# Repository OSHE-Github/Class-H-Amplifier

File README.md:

# Class-H-Amplifier

# Project Overview
This project aims to develop a lower-cost Class H amplifier design that can be used not only for audio, but other applications as well with little-to-no modification required. The design is based around a class AB amplifier like many reference designs. This amplifier design includes  documentation on testing and simulations to allow for easy replicability and modification. Key specifications and their impact on performance have been researched and were used to guide the design process. The design has been broken up into sections and most have been successfully simulated. These sections are shown in the block diagram.

# Methodology
The class H amplifier was broken down into sections to design separately that would fit together in the end. A class H amplifier differs from other amplifier classes due to its modulating supply rails [1]. A class AB amplifier was frequently used in reference designs and is commonly used especially in audio applications, leading that class to be the choice for this design as well. 

Specifications were defined throughout the process, both to guide the design and to evaluate the actual performance of the completed design. Common amplifier specifications listed on commercial designs include those shown in Table 1, including more which do not apply, are difficult to set a target for,  or are not easily testable. Target values were defined based on typical values and on what was a reasonable goal for this project. The specifications and their values are listed in the table below. 

| Specification | Target |
|--------------|--------|
| Maximum Output Power (Avg) | 100 W |
| Load Impedance | 8 Ω |
| Supply | ±6–45 V |
| Frequency Response | 20 Hz – 20 kHz |
| Total Harmonic Distortion (THD) | < 1% @ 1 kHz |
| Total Harmonic Distortion + Noise (THD+N) | < 1% @ 1 kHz |
| Signal to Noise Ratio (SNR) | ≥ 70 dB |
| Slew Rate | ≥ 5 V/µs |
| Efficiency | > 50% |
| Protection | Overvoltage, undervoltage, reverse polarity, undercurrent |

The full methodology is explained in more detail in the [project report](https://github.com/OSHE-Github/Class-H-Amplifier/blob/main/Documents/Class%20H%20Report.pdf).

# Bill of Materials
### Rail Follower
| Part Description                         | Part Number              | Quantity | Unit Cost | Total Cost |
|-----------------------------------------|--------------------------|----------|-----------|------------|
| 3.3 µH Sepic Inductor                   | ETQ-P8M3R3JFA            | 2        | $2.34     | $4.68      |
| 1 µF Sepic Medium Frequency Cap         | CL31B105KCHNFNE          | 50       | $0.10     | $5.21      |
| MOSFET N-Channel 100V                  | SIR870DP-T1-GE3          | 1        | $3.23     | $3.23      |
| 120 V 20A Output Diode                 | FSV20120V                | 1        | $1.30     | $1.30      |
| 10 mΩ 3W Shunt Resistor                | CRA2512-FZ-R010ELF       | 2        | $0.55     | $1.10      |
| 0.22 µF Soft Start Capacitor           | C3216X7R2A224K115AA      | 1        | $0.26     | $0.26      |
| 44.2 kΩ Rt Resistor                    | CRCW040244K2FKEDC        | 3        | $0.10     | $0.30      |
| 10 kΩ Resistor                         | RC0402FR-0710KL          | 4        | $0.10     | $0.40      |
| 22 kΩ Comp Resistor                    | ERA-2AEB223X             | 1        | $0.10     | $0.10      |
| 4700 pF Comp Capacitor                 | GRM155R72A472KA01D       | 1        | $0.10     | $0.10      |
| 330 µF Output Filter Capacitor         | EKXJ161ELL331MK50S       | 4        | $2.98     | $11.92     |
| Test Points                            | 36-5000-ND               | 7        | $0.28     | $1.96      |
| XT-30                                  | FIT0586                  | 2        | $1.90     | $3.80      |
| 7.5 kΩ Resistor                        | ERA-2AEB752X             | 3        | $0.10     | $0.30      |
| 110 kΩ Resistor                        | 311-110KLRCT-ND          | 1        | $0.10     | $0.10      |
| 10 µF ±10% 50V Input Capacitors        | CL31A106KBHNNNE          | 10       | $0.21     | $2.10      |
| TL072CDT Op-Amp                        | TL072CDT                 | 1        | $0.37     | $0.37      |
| 10 kΩ Potentiometer                    | PDB181-K220K-103B        | 1        | $1.40     | $1.40      |
| Signal Rectifier                       | BAS4002ARPPE6327HTSA1    | 1        | $0.32     | $0.32      |
| 3.5mm Audio Jack                       | SJ1-3523N                | 1        | $0.91     | $0.91      |

### Rail Splitter
| Part Description                         | Part Number                          | Quantity | Unit Cost | Total Cost |
|-----------------------------------------|--------------------------------------|----------|-----------|------------|
| Half-Bridge Gate Driver IC              | IRS21531DSTRPBFCT-ND                 | 2        | $1.24     | $2.48      |
| MOSFET N-CH 100V                        | SIR870DP-T1-GE3CT-ND                 | 4        | $3.23     | $12.92     |
| AD820ARZ Op-Amp                         | 505-AD820ARZ-ND                      | 2        | $9.11     | $18.22     |
| 10 µH Inductor                          | PCD2433CT-ND                         | 5        | $1.13     | $5.65      |
| Zener Diode                             | 1655-SK56BCT-ND                      | 5        | $0.49     | $2.45      |
| 5.6 kΩ 0.1% 1/10W                       | YAG1699CT-ND                         | 10       | $0.06     | $0.59      |
| 1 nF 1% 25V                             | 399-C0603C102F3GACTUCT-ND            | 10       | $0.50     | $5.04      |
| 10 µF ±20% 100V                         | 490-GRM32EC72A106ME05KCT-ND          | 15       | $0.64     | $9.56      |
| 10 µF ±10% 25V                          | 399-11939-1-ND                       | 10       | $0.13     | $1.26      |
| 470 µF 100 V                            | 493-1379-ND                          | 10       | $1.09     | $10.92     |
| 47 µF 100 V                             | 493-1147-ND                          | 10       | $0.28     | $2.80      |
| 10k Trimmer Pot                         | TC33X-103ECT-ND                      | 3        | $0.25     | $0.75      |
| 2200 pF ±20% 25V Ceramic                | 399-C0603C222M3RACTUCT-ND            | 10       | $0.15     | $1.47      |
| 0.1 µF ±10% 25V Ceramic                 | 399-C0603C104K3RACTUCT-ND            | 10       | $0.01     | $0.10      |
| 33 kΩ ±0.1% 0.1W                        | P33KDBCT-ND                          | 10       | $0.06     | $0.61      |
| 330 Ω ±5% 0.1W                          | 311-330GRCT-ND                       | 10       | $0.02     | $0.20      |
| 3.9 kΩ ±1% 0.1W                         | RMCF0603FT3K90CT-ND                  | 10       | $0.01     | $0.06      |
| 12 kΩ ±0.1% 0.1W                        | P12KDBCT-ND                          | 10       | $0.06     | $0.61      |
| 3.3 kΩ ±1% 0.1W                         | RMCF0603FT3K30CT-ND                  | 10       | $0.01     | $0.06      |
| 82 kΩ ±5% 0.1W                          | 311-82KGRCT-ND                       | 10       | $0.01     | $0.07      |
| 4.7 kΩ ±1% 0.1W                         | RMCF0603FT4K70CT-ND                  | 10       | $0.01     | $0.06      |
| 10 Ω ±1% 0.1W                           | RMCF0603FT10R0CT-ND                  | 10       | $0.01     | $0.06      |
| 1.5 kΩ ±1% 0.25W                        | RHM1.50KADCT-ND                      | 10       | $0.08     | $0.75      |
| Test Point                              | 36-5005-ND                           | 30       | $0.26     | $7.68      |

### Class AB Amplifier
| Part Number                         | Part Description                     | Quantity | Unit Cost | Total Cost |
|------------------------------------|-------------------------------------|----------|-----------|------------|
| 296-41370-2-ND                     | OPA454 Op-Amp                       | 1        | $7.18     | $7.18      |
| MJL21193GOS-ND                     | Output PNP BJT 250 V 16 A           | 1        | $6.26     | $6.26      |
| MJL21194GOS-ND                     | Output NPN BJT 250 V 16 A           | 1        | $6.26     | $6.26      |
| MJE15033GOS-ND                     | Driver PNP BJT 250 V 8 A            | 2        | $2.10     | $4.20      |
| MJE15032GOS-ND                     | Driver NPN BJT 250 V 8 A            | 2        | $2.10     | $4.20      |
| TTC004BQ-ND                        | NPN 160V 1.5A                       | 3        | $0.90     | $2.70      |
| TTA004BQ-ND                        | PNP 160V 1.5A                       | 2        | $0.81     | $1.62      |
| 541-WSLF3222L4000FE6CT-ND          | Output Emitter Resistors 12W         | 2        | $3.01     | $6.02      |
| 541-CRCW080540K0FKEACT-ND          | 40 kΩ Resistor 1/4W                 | 2        | $0.12     | $0.24      |
| 541-4187-1-ND                      | 20 kΩ Resistor 1/4W                 | 1        | $0.10     | $0.10      |
| 541-1.00KCCT-ND                    | 1 kΩ Resistor 1/4W                  | 2        | $0.10     | $0.20      |
| 541-1.10KCCT-ND                    | 1.1 kΩ Resistor 1/4W                | 1        | $0.10     | $0.10      |
| 311-3.60KFRCT-ND                   | 3.6 kΩ Resistor 1/4W                | 1        | $0.10     | $0.10      |
| 541-100CCT-ND                      | 100 Ω Resistor 1/4W                 | 3        | $0.10     | $0.30      |
| 709-VPDD202W102K1GV001ECT-ND       | 1 nF Filter Capacitor               | 1        | $0.17     | $0.17      |
| 399-C1206C104K5RACTUCT-ND          | 0.1 µF Bypass Capacitors            | 2        | $0.08     | $0.16      |
| 478-12065A300JAT2ACT-ND            | 30 pF Capacitor                     | 1        | $0.28     | $0.28      |
| 1712-CRGH1206F330RCT-ND            | 330 Ω Resistor 1/2W                 | 1        | $0.10     | $0.10      |
| 118-PV36W102C01B00-ND              | 1 kΩ Potentiometer                  | 1        | $1.53     | $1.53      |

## Enclosure
| Part Description                          | Qty | Link        | Cost  |
|-------------------------------------------|-----|------------|-------|
| #2 x 1/4" Pan Head Sheet Metal Screw      | 12  | [Link](https://www.amazon.com/dp/B094XVJRQB?ref=cm_sw_r_cso_cp_apin_dp_TH6723NY6FKN1X2NP8HY&ref_=cm_sw_r_cso_cp_apin_dp_TH6723NY6FKN1X2NP8HY&social_share=cm_sw_r_cso_cp_apin_dp_TH6723NY6FKN1X2NP8HY&oas=true)  | $7.49 |
| 3mm x 20mm Hex Bolt                       | 4   | [Link](https://www.amazon.com/BNUOK-Socket-Screws-Threads-Spanner/dp/B0DJR2Q5LP/ref=sr_1_3?crid=W2305ZD2FNQV&dib=eyJ2IjoiMSJ9.P3m1jdOV6NjRNryhqc6mNZYJ_rSOVjPZwx3x_IZUzmfyR4svjfvJ8AZDbHj88V6uT6GKq76S7kONkJRhTa5xslJtBGZexPCsansF_fme_kHCfzFpS4c3M_CYCkMVQ_ypZ0WC17a0_ok_aXVGSjp6NNtctOxYpODZq_4g6q-cFWu1m7xF6YFGcT4afU0DKKKk5LrJtV_EwZtWg0IahqVlrof1_2IzW9kSKOxP0gJua7HT48TAWBmCF_ZQ22wekv2fIo_w5N-S9Ny5Abupu7aoxaTT8c5O8pXYQZHBffv8LWM.cO3imLAJvC58IygrIHBa3FQS2-P8iiNmOXqj3alLTTM&dib_tag=se&keywords=20mm%2Bby%2B3mm%2Bbolt&qid=1776456512&s=industrial&sprefix=20mm%2Bby%2B3mm%2Bbol%2Cindustrial%2C128&sr=1-3&th=1)  | $7.49 |
| M3-0.5mm Hex Nut                          | 4   | [Link](https://www.amazon.com/ZQZ-M3-0-5mm-Stainless-Hardware-Standard/dp/B0CQJK2R5T/ref=sr_1_1_sspa?crid=3UUTX6CCJ48UD&dib=eyJ2IjoiMSJ9.oMLvADkOWoV2tdSD99yJKn77P0sYpqhahu07OuJaMVkT508_3DnS36jHQzzZcHaUcGwyuyrUUh6WKSawD0OY-kWypDtqByUyagUa8YG9794kMQc0sju8xYS97ldZXOMoD6u6WHuXXNEtnw-eQlqEG0MCaJLsESe1SBe6NfDM2q7kQrNBBYxnpDQhaXQ0WjLJOGpQ7I9LhlCe8ay9Hv0y8ibHUIxIMg4l7bJQl-S25i2cHnJW84qivJMa57IFFInZ1vuLvxHl58jHhJaIxB-g1VpELbbkeuYo2Ii8aOXYYqE.eCEfIdI_MtNjLMBC5TwFn8KkcLCQMYQUdiLAK9wA-Sc&dib_tag=se&keywords=M3%2Bnut&qid=1776456979&s=industrial&sprefix=m3%2B%2Cindustrial%2C248&sr=1-1-spons&sp_csd=d2lkZ2V0TmFtZT1zcF9hdGY&th=1)  | $9.99 |

# Tools Used
| Part Description | Part Number | Cost |
|------------|------------------|----------|
| Soldering Iron | FX888DX-010BY | $122.99 |
| Oscilliscope | DSOX2004A |  $3306.90 |
| B07BR3F9N6 | 3D Printer |  $169.00 |

Software:
- [LTspice](https://www.analog.com/en/resources/design-tools-and-calculators/ltspice-simulator.html)
- [KiCAD](https://www.kicad.org/download/)
  
# Assembly Overview
1. Gather materials specified in BOM
2. Order materials using provided Gerber files
3. Solder componenents on PCB as specified by schematics
4. Test as described in the [testing procedure](https://github.com/OSHE-Github/Class-H-Amplifier/blob/main/Documents/Testing%20Procedure.md)
5. Dowload enclosure files
6. 3D print enclosure
7. Secure PCBs in enclosure

Detailed assembly guide, including details on LTspice simulations can be found in the [project report](https://github.com/OSHE-Github/Class-H-Amplifier/blob/main/Documents/Class%20H%20Report.pdf)

# Future Recommendations
1. Further testing  for the final rendition of the rail follower board separately and the combination of the rail follower, rail splitter, and AB amplifier
2. Improve distortion, potentially through modification on rail splitter board
3. Further testing is needed for that to understand its maximum load conditions and how those can be improved
4. Additional testing with distortion using more precise equipment or measurement techniques

# References
[1] N. Utomo et al., “An 85.1% Peak Efficiency, Low Power Class H Audio Amplifier With Full Class H Operation,” *IEEE Transactions on Circuits and Systems I: Regular Papers*, vol. 70, no. 12, pp. 1–13, 2023. doi: 10.1109/TCSI.2023.3305622.

[2] S. Munz, “Slew Rate in Audio Amplifiers - What Does it Mean?,” *Audioholics*, Feb. 08, 2013.  
https://www.audioholics.com/audio-amplifier/amplifier-slew-rate

[3] Cambridge Audio, “Amplifier Specifications,” *Cambridge Audio*.  
https://www.cambridgeaudio.com/usa/en/blog/amplifier-specifications

[4] “What is Total Harmonic Distortion (THD)?,” *Audiophile On*, Aug. 16, 2025.  
https://www.audiophileon.com/news/what-is-total-harmonic-distortion-thd

[5] V. Batra, “Modular Concepts: What is an Envelope Follower?,” *Perfect Circuit*, Aug. 22, 2024.  
https://www.perfectcircuit.com/signal/envelope-followers

[6] “What’s the difference between MOSFET and BJT and how to choose?,” *NextPCB*.  
https://www.nextpcb.com/blog/what-is-the-difference-between-mosfet-and-bjt-and-how-to-choose

[7] A. Sedra and K. Smith, *Microelectronic Circuits*. Oxford University Press, 2019.

[8] O. Jørgensen, “What do different amplifier classes mean?,” *Dynaudio*, May 14, 2025.  
https://dynaudio.com/magazine/2025/may/amplifier-classes-ask-the-expert

[9] D. Self, *Audio Power Amplifier Design*, 6th ed. Elsevier / Focal Press, 2013.

[10] Cadence PCB Solutions, “What is Signal to Noise Ratio and How to calculate it?,” 2023.  
https://resources.pcb.cadence.com/blog/2020-what-is-signal-to-noise-ratio-and-how-to-calculate-it

[11] “OSHW,” *Freedom Defined*, 2023.  
https://freedomdefined.org/OSHW

This was also used as a general reference for various amplifier topics and designs that were not directly referenced in this report:

[12] B. Cordell, *Designing Audio Power Amplifiers*. McGraw-Hill Professional, 2010.

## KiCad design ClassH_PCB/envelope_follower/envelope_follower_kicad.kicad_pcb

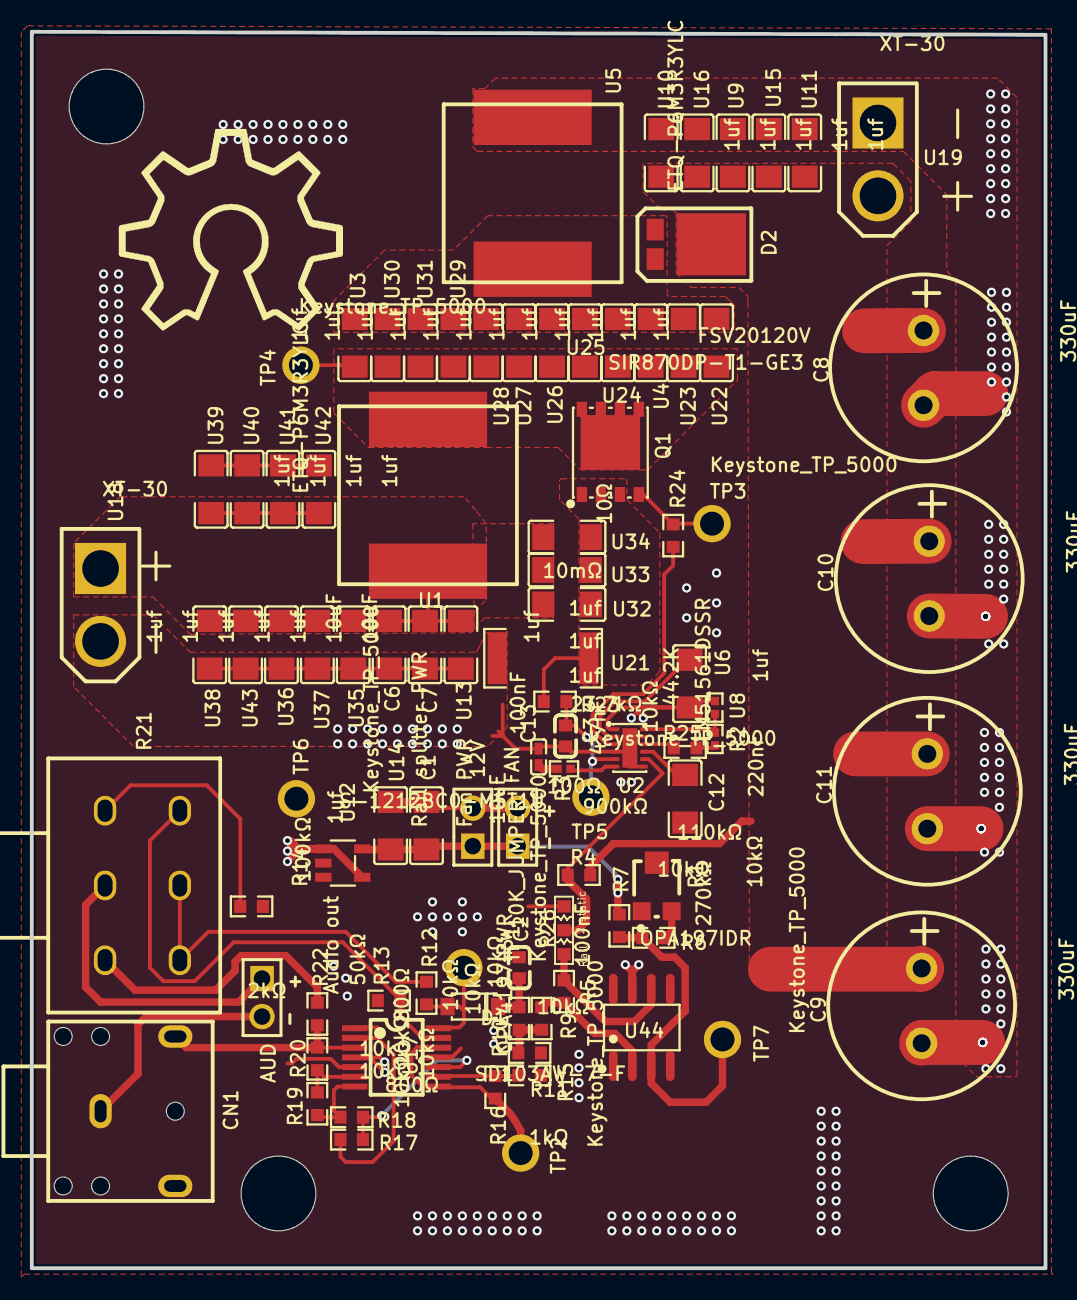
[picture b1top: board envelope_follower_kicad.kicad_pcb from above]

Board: 4 copper layers, 67.8 x 82.7 mm, 95 parts (0 on the bottom side), 36 nets.

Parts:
12V: Rail splitter PWR; HDR-M-2.54_1X2
AUD: Audio out; HDR-M-2.54_1X2
C1, C6, C7: 10uF; C1206
C2, C3: 100nF; C0603
C8, C9, C10, C11: 330uF; CAP-TH_BD12.5-P5.00-D0.6-FD
C12: 220nF; C1206
C13: 4.7nF; C0402
CN1: SJ1-3523N; AUDIO-TH_SJ1-3523N
D1: SD103AW-7-F; SOD-123_L2.8-W1.8-LS3.7-RD
D2: FSV20120V
FAN: Fan PWR; HDR-M-2.54_1X2
Hole_gge10732: Hole_gge10732
Hole_gge10771: Hole_gge10771
Hole_gge10801: Hole_gge10801
Q1: SIR870DP-T1-GE3; POWERPAK-SO-8_L5.9-W4.9-P1.27-BL-EP
R1: 10kΩ; RES-ADJ-SMD_3P-L3.0-W3.8-P1.75-BR
R2: 10kΩ; R0402
R3: 23.7kΩ; R0402
R4: 900kΩ; R0603
R5, R6, R9, R10, R15, R16, R17, R18, R19, R20: 10kΩ; R0603
R7: 270kΩ; R0603
R11: 1kΩ; R0603
R12: 50kΩ; R0603
R13, R22: 800Ω; R0603
R14: 100kΩ; RES-ADJ-TH_PDB182-K220K-104B
R21: 2kΩ; R0603
R23: 100Ω; R0603
R24: 10Ω; R0603
R25: 110kΩ; R0603
R26: 10K_JUMPER; RESISTOR_JUMPER_3
TP1, TP2, TP3, TP4, TP5, TP6, TP7: Keystone_TP_5000; KEYSTONE_TP_5000
U1, U5: ETQ-P6M3R3YLC; INDUCTOR FOOTPRINT 10.9*10
U2: LM51561DSSR; WSON-12_L3.0-W2.0-P0.5-BL-EP2.7
U3, U4, U6, U9, U10, U11, U13, U14, U15, U16, U22, U23, U24, U25, U26, U27, U28, U29, U30, U31, U32, U33, U34, U35, U36, U37, U38, U39, U40, U41, U42, U43: 1uf; C1206
U8: 44.2K; R0402
U12: S-1212BC0-M5T1U; SOT-23-5_L2.9-W1.6-P0.95-LS2.8-TL
U17: OPA4197IPWR; TSSOP-14_L5.0-W4.4-P0.65-LS6.4-BL
U18, U19: XT-30
U21: 10mΩ; R2512
U44: OPA197IDR; SOIC-8_L4.9-W3.9-P1.27-LS6.0-BL

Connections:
CN1_3: CN1.3, R20.1, R22.2, U17.3
D2_2: C8.1, C9.1, C10.1, C11.1, D2.2, R4.2, U9.2, U10.2, U11.2, U15.2, U16.2, U19.2
GND: 12V.2, AUD.2, C1.1, C2.1, C3.1, C6.1, C7.1, C8.2, C9.2, C10.2, C11.2, C12.2, C13.1, CN1.1, FAN.2, R1.2, R2.1, R11.1, R13.2, R15.2, R21.1, R25.1, R26.3, TP6.1, U2.4, U2.7, U2.13, U5.1, U9.1, U10.1, U11.1, U12.2, U13.2, U14.2, U15.1, U16.1, U17.5, U17.11, U18.2, U19.1, U21.1, U35.1, U36.1, U37.1, U38.1, U39.1, U40.1, U41.1, U42.1, U43.1, U44.4
Q1_3: Q1.1, Q1.2, Q1.3, R23.2, U21.2, U32.1, U33.1, U34.1
Q1_4: Q1.4, R24.2, TP3.1
Q1_8: Q1.5, Q1.6, Q1.7, Q1.8, TP4.1, U1.2, U3.1, U4.1, U22.1, U23.1, U24.1, U25.1, U26.1, U27.1, U28.1, U29.1, U30.1, U31.1
R1_3: R1.3, R6.2
R3_1: C13.2, R3.1
R6_1: R6.1, R7.2, TP7.1, U44.3
R9_1: R9.1, R10.1, R11.2
R10_2: C2.2, D1.1, R10.2
R12_2: R12.2, R14.5, R14.6
R14_1: R14.1, R21.2
R14_2: AUD.1, R14.2
R14_3: R14.3, R22.1
U2_2: U2.2, U6.1
U2_3: R24.1, U2.3
U2_5: C3.2, R23.1, TP5.1, U2.5
U2_6: R3.2, U2.6
U2_8: R4.1, R26.2, U2.8
U2_9: C12.1, U2.9
U2_10: R25.2, U2.10
U2_12: R2.2, U2.12, U8.1
U3_2: D2.1, U3.2, U4.2, U5.2, U22.2, U23.2, U24.2, U25.2, U26.2, U27.2, U28.2, U29.2, U30.2, U31.2
U12_5: 12V.1, C1.2, FAN.1, R7.1, U12.5, U14.1
U17_1: R17.1, U17.1, U17.2
U17_6: R19.1, R20.2, U17.6
U17_7: R18.1, R19.2, U17.7
U17_8: R16.1, TP2.1, U17.8, U17.12
U17_9: R15.1, R16.2, U17.9
U17_10: R17.2, R18.2, U17.10
U17_13: R13.1, R14.4, U17.13
U17_14: D1.2, R12.1, TP1.1, U17.14
U44_2: R5.1, R9.2, U44.2
U44_6: R5.2, R26.1, U44.6
VCC: C6.2, C7.2, U1.1, U2.1, U6.2, U8.2, U12.1, U12.4, U13.1, U17.4, U18.1, U32.2, U33.2, U34.2, U35.2, U36.2, U37.2, U38.2, U39.2, U40.2, U41.2, U42.2, U43.2, U44.7

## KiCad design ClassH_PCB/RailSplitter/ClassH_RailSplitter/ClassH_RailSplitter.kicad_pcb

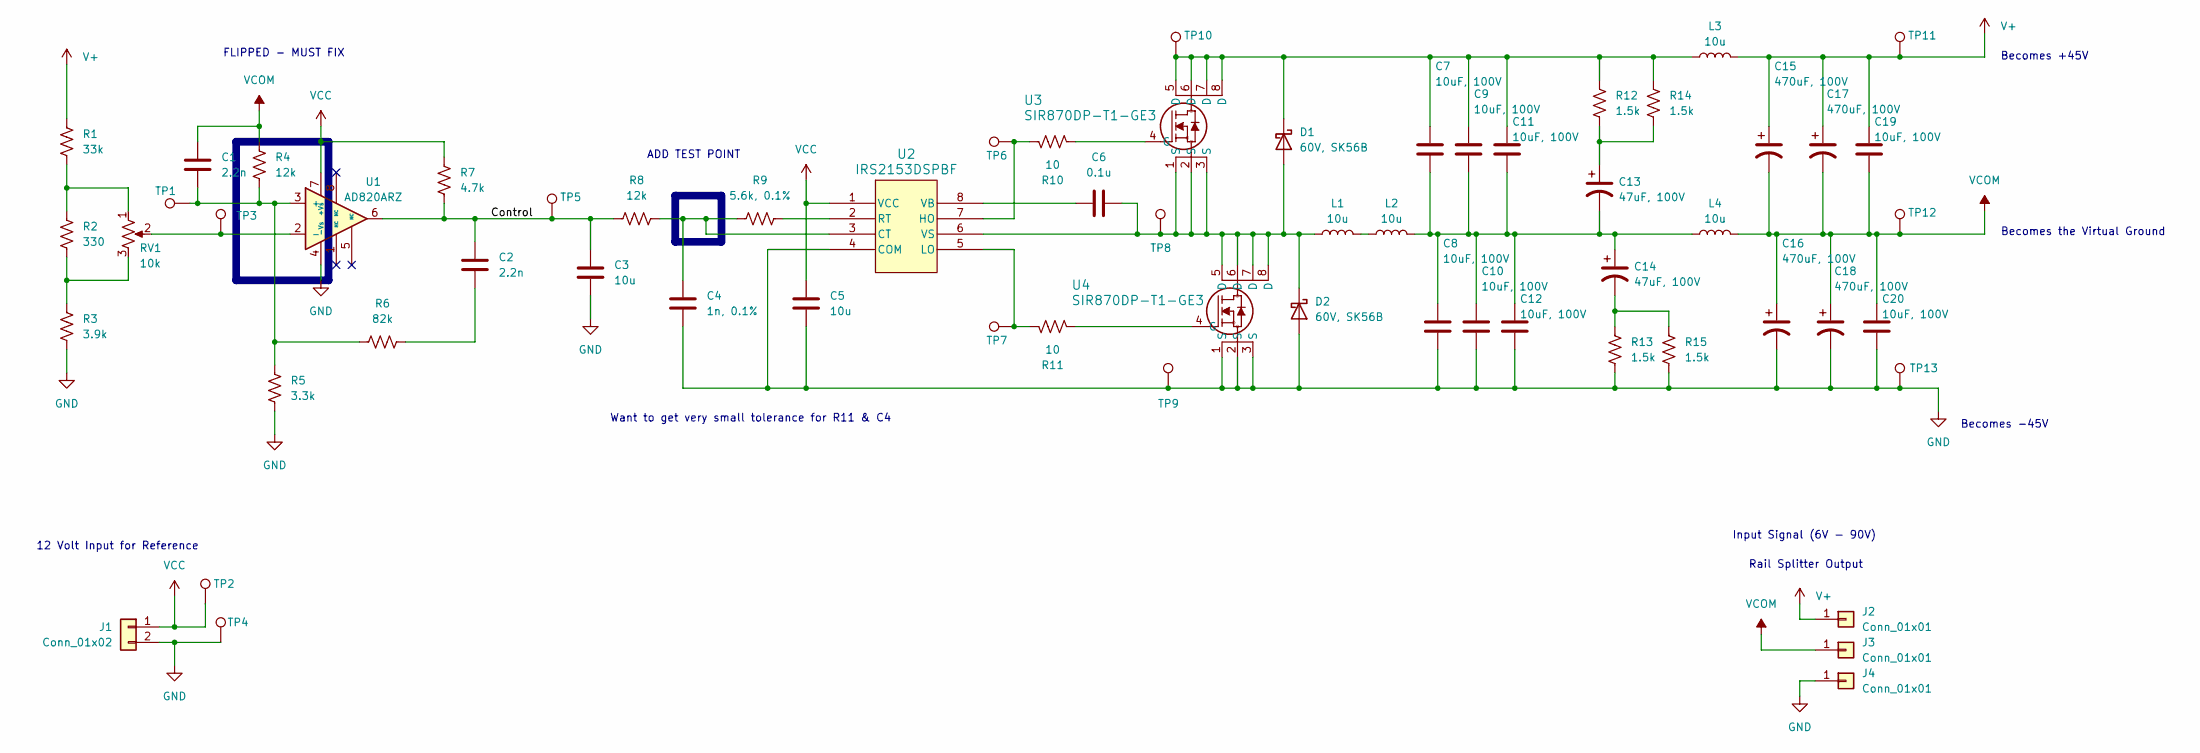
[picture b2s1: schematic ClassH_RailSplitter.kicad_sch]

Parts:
C1, C2: 2.2n; C_0603_1608Metric_Pad1.08x0.95mm_HandSolder
C3, C5: 10u; C_0805_2012Metric_Pad1.18x1.45mm_HandSolder
C4: 1n, 0.1%; C_0603_1608Metric_Pad1.08x0.95mm_HandSolder
C6: 0.1u; C_0603_1608Metric_Pad1.08x0.95mm_HandSolder
C7, C8, C9, C10, C11, C12, C19, C20: 10uF, 100V; C_1210_3225Metric_Pad1.33x2.70mm_HandSolder
C13, C14: 47uF, 100V; CP_Radial_D10.0mm_P5.00mm
C15, C16, C17, C18: 470uF, 100V; CP_Radial_D16.0mm_P7.50mm
D1, D2: 60V, SK56B; D_SMB_Handsoldering
J1: Conn_01x02; TerminalBlock_MaiXu_MX126-5.0-02P_1x02_P5.00mm
J2, J3, J4: Conn_01x01; MountingHole_5mm_Pad_TopBottom
L1, L2, L3, L4: 10u; IND_ETQP5M100YFC
R1: 33k; R_0603_1608Metric_Pad0.98x0.95mm_HandSolder
R2: 330; R_0603_1608Metric_Pad0.98x0.95mm_HandSolder
R3: 3.9k; R_0603_1608Metric_Pad0.98x0.95mm_HandSolder
R4, R8: 12k; R_0603_1608Metric_Pad0.98x0.95mm_HandSolder
R5: 3.3k; R_0603_1608Metric_Pad0.98x0.95mm_HandSolder
R6: 82k; R_0603_1608Metric_Pad0.98x0.95mm_HandSolder
R7: 4.7k; R_0603_1608Metric_Pad0.98x0.95mm_HandSolder
R9: 5.6k, 0.1%; R_0603_1608Metric_Pad0.98x0.95mm_HandSolder
R10, R11: 10; R_0603_1608Metric_Pad0.98x0.95mm_HandSolder
R12, R13, R14, R15: 1.5k; R_0603_1608Metric_Pad0.98x0.95mm_HandSolder
RV1: 10k; Potentiometer_Bourns_TC33X_Vertical
TP1, TP2, TP3, TP4, TP5, TP6, TP7, TP8, TP9, TP10, TP11, TP12, TP13: TestPoint; TestPoint_Keystone_5005-5009_Compact
U1: AD820ARZ; SOIC127P600X175-8N; MPN AD820ARZ-REEL-REEL7
U2: IRS2153DSPBF; SOIC8_INF
U3, U4: SIR870DP-T1-GE3; MOSFET_7DP-T1-GE3_VIS

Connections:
/Control: C2.1, C3.1, R7.2, R8.1, TP5.1, U1.6
GND: C3.2, C4.2, C5.2, C8.1, C10.1, C12.1, C16.2, C18.2, C20.1, D2.2 (A), J1.2, J4.1, R3.1, R5.1, R13.1, R15.1, TP4.1, TP9.1, TP13.1, U1.4 (-Vs), U2.4 (COM), U4.1 (S), U4.2 (S), U4.3 (S)
unnamed: C2.2, R6.2
unnamed: C7.1, C8.2, C9.1, C10.2, C11.1, C12.2, C13.2, C14.1, L2.2, L4.1
unnamed: C13.1, R12.1, R14.1
unnamed: C14.2, R13.2, R15.2
unnamed: C6.2, D1.2 (A), D2.1 (K), L1.1, TP8.1, U2.6 (VS), U3.1 (S), U3.2 (S), U3.3 (S), U4.5 (D), U4.6 (D), U4.7 (D), U4.8 (D)
unnamed: C7.2, C9.2, C11.2, D1.1 (K), L3.1, R12.2, R14.2, TP10.1, U3.5 (D), U3.6 (D), U3.7 (D), U3.8 (D)
unnamed: L1.2, L2.1
unnamed: R1.2, R2.2, RV1.1
unnamed: R2.1, R3.2, RV1.3
unnamed: C1.2, R4.1, R5.2, R6.1, TP1.1, U1.3 (+)
unnamed: RV1.2, TP3.1, U1.2 (-)
unnamed: C4.1, R8.2, R9.1, U2.3 (CT)
unnamed: R10.1, TP6.1, U2.7 (HO)
unnamed: R11.1, TP7.1, U2.5 (LO)
unnamed: R9.2, U2.2 (RT)
unnamed: C6.1, U2.8 (VB)
unnamed: R10.2, U3.4 (G)
unnamed: R11.2, U4.4 (G)
V+: C15.1, C17.1, C19.2, J2.1, L3.2, R1.1, TP11.1
VCC: C5.1, J1.1, R7.1, TP2.1, U1.7 (+Vs), U2.1 (VCC)
VCOM: C1.1, C15.2, C16.1, C17.2, C18.1, C19.1, C20.2, J3.1, L4.2, R4.2, TP12.1

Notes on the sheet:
Becomes +45V
ADD TEST POINT
Becomes the Virtual Ground
Want to get very small tolerance for R11 & C4
Rail Splitter Output
Input Signal (6V - 90V)
12 Volt Input for Reference
Becomes -45V
FLIPPED - MUST FIX

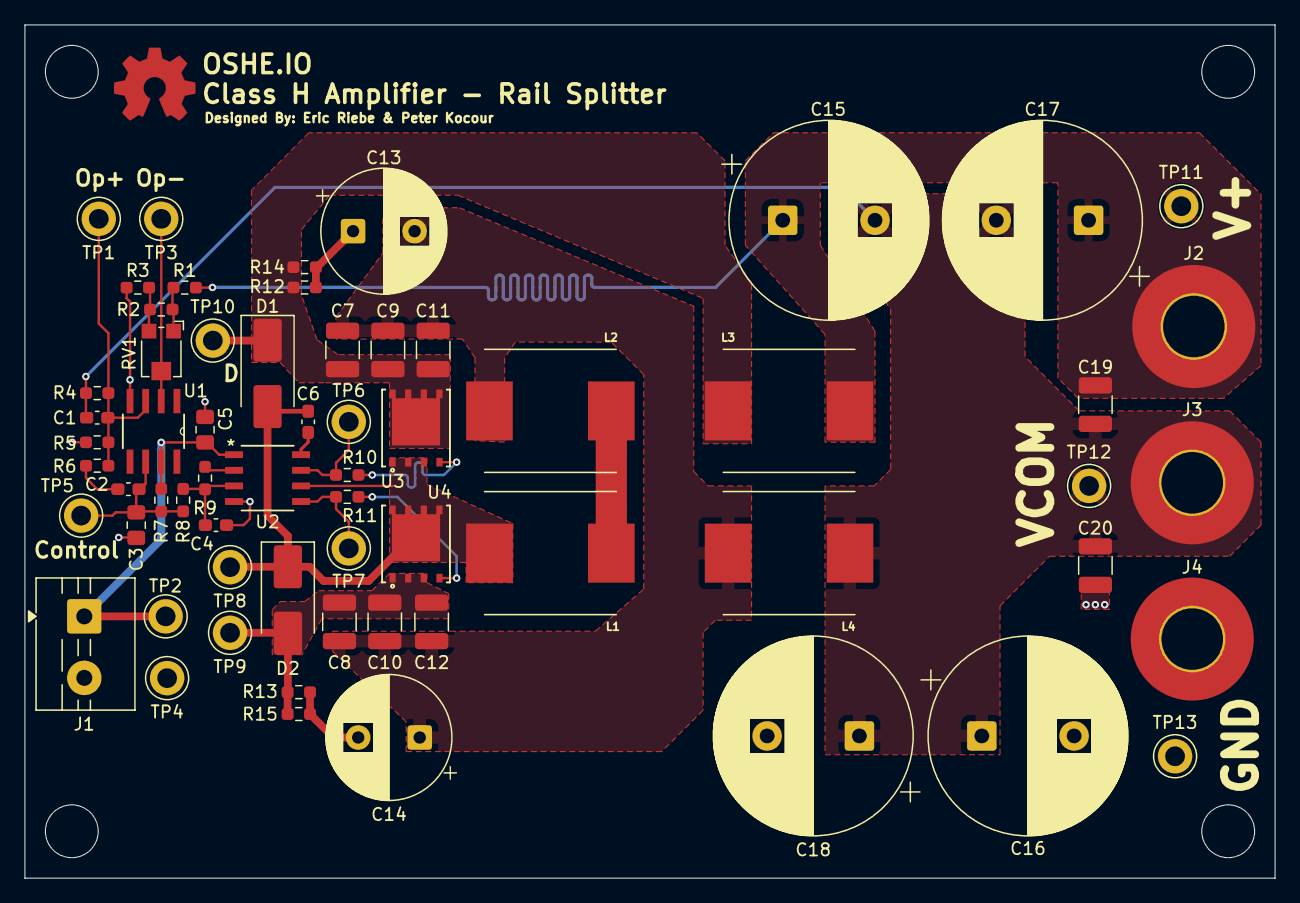
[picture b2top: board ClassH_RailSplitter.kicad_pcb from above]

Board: 2 copper layers, 101.6 x 69.3 mm, 63 parts (0 on the bottom side), 23 nets.

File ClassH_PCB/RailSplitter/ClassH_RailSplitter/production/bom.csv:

Designator,Footprint,Quantity,Value,LCSC Part #
"C1, C2",0603,2,2.2n,
"C10, C11, C12, C19, C20, C7, C8, C9",1210,8,"10uF, 100V",
"C13, C14",CP_Radial_D10.0mm_P5.00mm,2,"47uF, 100V",
"C15, C16, C17, C18",CP_Radial_D16.0mm_P7.50mm,4,"470uF, 100V",
"C3, C5",0805,2,10u,
C4,0603,1,"1n, 0.1%",
C6,0603,1,0.1u,
"D1, D2",D_SMB_Handsoldering,2,"60V, SK56B",
J1,TerminalBlock_MaiXu_MX126-5.0-02P_1x02_P5.00mm,1,Conn_01x02,
"J2, J3, J4",MountingHole_5mm_Pad_TopBottom,3,Conn_01x01,
"L1, L2, L3, L4",IND_ETQP5M100YFC,4,10u,
R1,0603,1,33k,
"R10, R11",0603,2,10,
"R12, R13, R14, R15",0603,4,1.5k,
R2,0603,1,330,
R3,0603,1,3.9k,
"R4, R8",0603,2,12k,
R5,0603,1,3.3k,
R6,0603,1,82k,
R7,0603,1,4.7k,
R9,0603,1,"5.6k, 0.1%",
RV1,Potentiometer_Bourns_TC33X_Vertical,1,10k,
"TP1, TP10, TP11, TP12, TP13, TP2, TP3, TP4, TP5, TP6, TP7, TP8, TP9",TestPoint_Keystone_5005-5009_Compact,13,TestPoint,
U1,SOIC127P600X175-8N,1,AD820ARZ,AD820ARZ-REEL-REEL7
U2,SOIC8_INF,1,IRS2153DSPBF,
"U3, U4",MOSFET_7DP-T1-GE3_VIS,2,SIR870DP-T1-GE3,

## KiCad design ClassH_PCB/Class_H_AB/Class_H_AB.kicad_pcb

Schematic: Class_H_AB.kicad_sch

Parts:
C1: 1n; C_1206_3216Metric_Pad1.33x1.80mm_HandSolder
C2: 30p; C_1206_3216Metric_Pad1.33x1.80mm_HandSolder
C3, C4: 0.1u; C_1206_3216Metric_Pad1.33x1.80mm_HandSolder
J1, J2, J3: TB002-500-02BE; CONN_TB002-500-02BE_CUD
Q1, Q3: Q_PNP_ECB; TO-126-3_Vertical
Q2, Q4, Q5: Q_NPN_ECB; TO-126-3_Vertical
Q6: MJL21194; TO545P2030X530X2900-3
Q7: MJL21193G; TO545P2030X530X2900-3; PARTREV 7
R1, R2: 1k; R_0805_2012Metric_Pad1.20x1.40mm_HandSolder
R3: 20k; R_1206_3216Metric_Pad1.30x1.75mm_HandSolder
R4, R9, R10: 100; R_0805_2012Metric_Pad1.20x1.40mm_HandSolder
R5, R6: 40k; R_0805_2012Metric_Pad1.20x1.40mm_HandSolder
R7: 3.6k; R_1206_3216Metric_Pad1.30x1.75mm_HandSolder
R8: 1.1k; R_0805_2012Metric_Pad1.20x1.40mm_HandSolder
R11: 330; R_1206_3216Metric_Pad1.30x1.75mm_HandSolder
R12, R13: 0.33; R_1020_2550Metric_Pad1.33x5.20mm_HandSolder
R14: PV36W102C01B00; POT_PV36W_MUR
TP1, TP2, TP3, TP4, TP5, TP6, TP7, TP8, TP9, TP10, TP11, TP12: 5000; KEYSTONE_5000; PARTREV H
U1: OPA454AIDDA; DDA0008J_NV
U2, U4: MJE15032G; TO-220AB_ONS
U3, U5: MJE15033G; TO-220AB_ONS

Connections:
/OUT: R4.1, TP1.TP, U1.6 (OUT)
/Rf: J1.1, R3.2, R12.2, R13.1, TP12.TP
/VDD: C3.1, J2.1, Q1.1 (E), Q6.2, R9.1, U1.7 (V+), U2.2 (C), U4.2 (C)
/VSS: C2.2, C4.1, J2.2, Q2.1 (E), Q7.2, R10.2, U1.1 (E_D_Com), U1.4 (V-), U3.3 (E), U5.3 (E)
GND: C1.2, C3.2, C4.2, J1.2, J3.1, R1.1, R5.2, R6.1
unnamed: J3.2, R2.2
unnamed: Q1.3 (B), Q3.1 (E), R9.2, TP10.TP
unnamed: Q1.2 (C), Q3.3 (B), R5.1
unnamed: Q2.3 (B), Q4.1 (E), R10.1, TP11.TP
unnamed: Q2.2 (C), Q4.3 (B), R6.2
unnamed: Q3.2 (C), Q5.2 (C), R7.1, TP2.TP, TP8.TP, U2.1 (B)
unnamed: Q4.2 (C), Q5.1 (E), R4.2, R8.2, TP3.TP, TP9.TP, U3.1 (B)
unnamed: Q5.3 (B), R14.2
unnamed: Q6.3, R12.1, TP6.TP
unnamed: Q7.3, R13.2, TP7.TP
unnamed: R7.2, R14.1
unnamed: R8.1, R14.3
unnamed: C2.1, U1.8 (E_D)
unnamed: C1.1, R2.1, U1.3 (IN+)
unnamed: R1.2, R3.1, U1.2 (IN-)
unnamed: U2.3 (E), U4.1 (B)
unnamed: U3.2 (C), U5.1 (B)
unnamed: Q6.1, R11.1, TP4.TP, U4.3 (E)
unnamed: Q7.1, R11.2, TP5.TP, U5.2 (C)

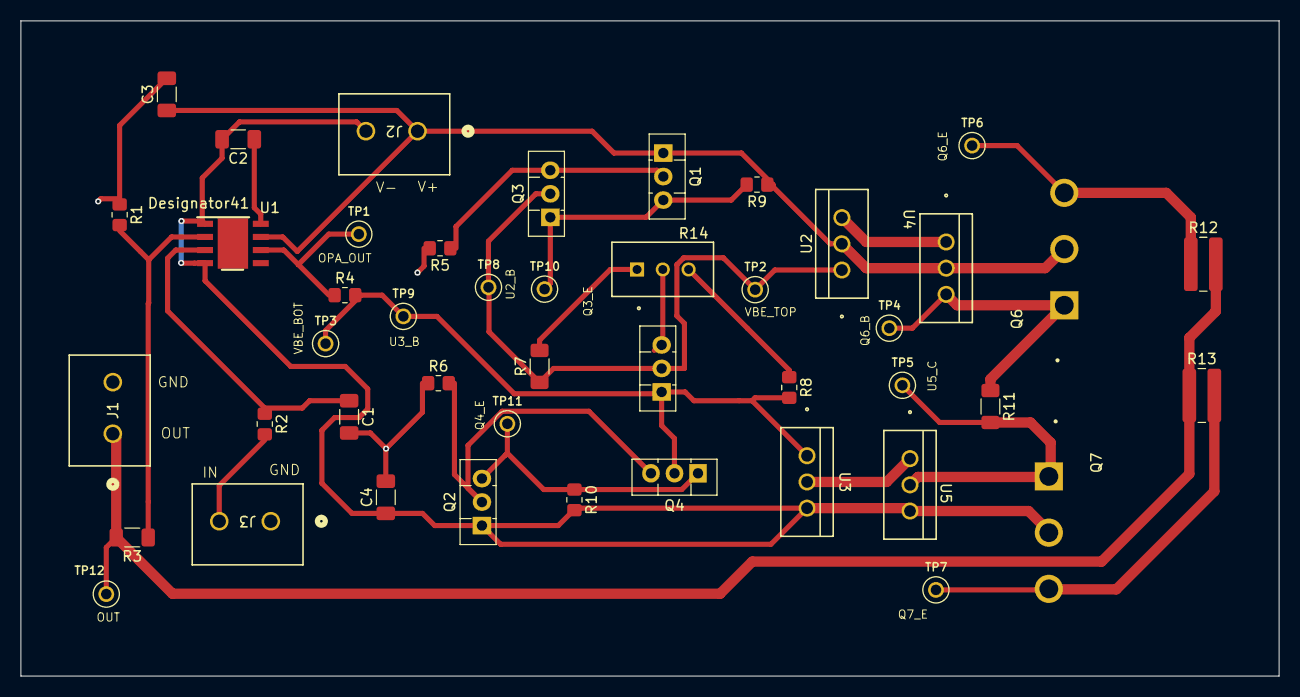
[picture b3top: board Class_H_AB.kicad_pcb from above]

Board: 2 copper layers, 122.0 x 63.5 mm, 45 parts (0 on the bottom side), 24 nets.

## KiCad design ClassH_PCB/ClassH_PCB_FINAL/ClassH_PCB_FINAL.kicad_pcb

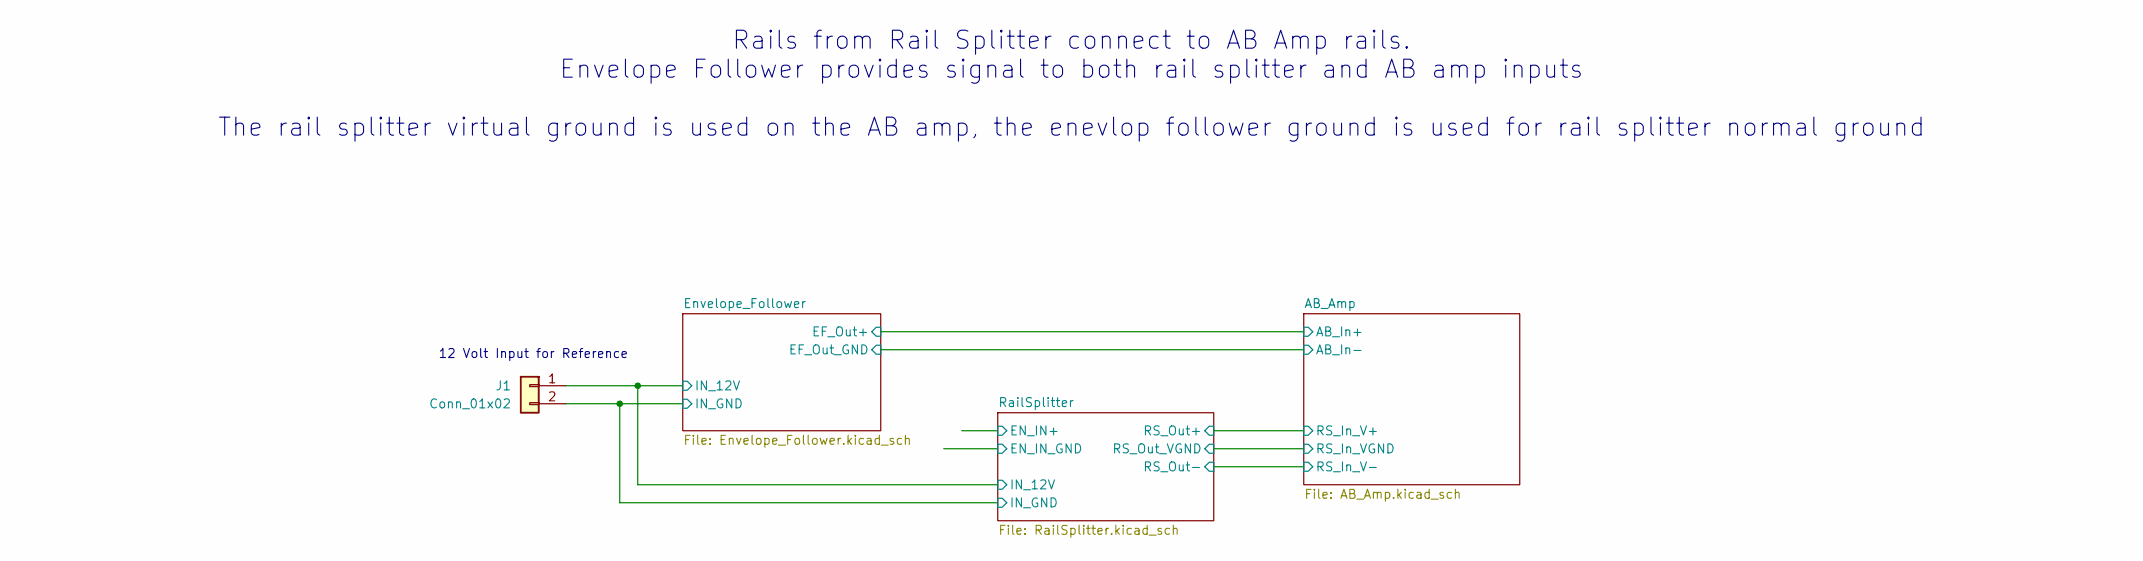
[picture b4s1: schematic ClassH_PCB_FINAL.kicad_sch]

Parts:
J1: Conn_01x02; TerminalBlock_MaiXu_MX126-5.0-02P_1x02_P5.00mm

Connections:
GND: J1.2; also elsewhere on the board
VCC: J1.1; also elsewhere on the board

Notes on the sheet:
Rails from Rail Splitter connect to AB Amp rails. Envelope Follower provides signal to both rail splitter and AB amp inputs The rail splitter virtual ground is used on the AB amp, the enevlop follower ground is used for rail splitter normal ground
12 Volt Input for Reference

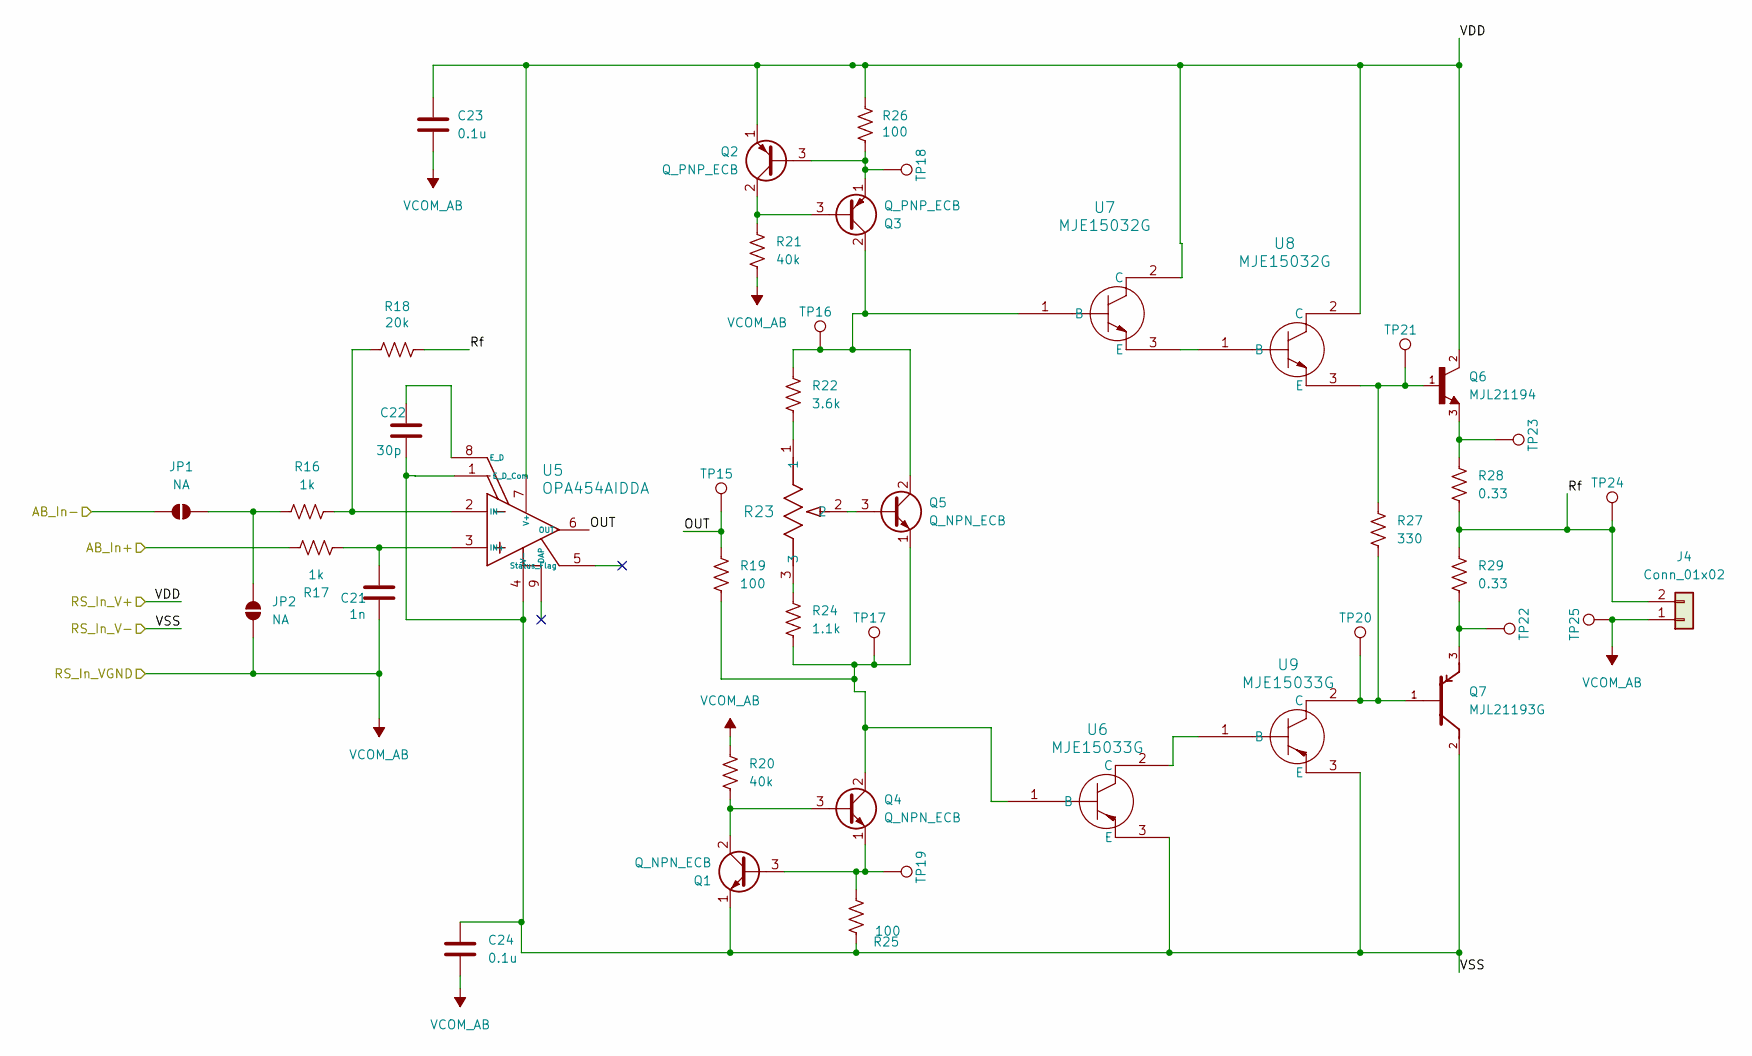
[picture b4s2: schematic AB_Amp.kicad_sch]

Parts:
C21: 1n; C_1206_3216Metric_Pad1.33x1.80mm_HandSolder
C22: 30p; C_1206_3216Metric_Pad1.33x1.80mm_HandSolder
C23, C24: 0.1u; C_1206_3216Metric_Pad1.33x1.80mm_HandSolder
J4: Conn_01x02; TerminalBlock_MaiXu_MX126-5.0-02P_1x02_P5.00mm
JP1, JP2: NA; SolderJumper-2_P1.3mm_Open_Pad1.0x1.5mm
Q1, Q4, Q5: Q_NPN_ECB; TO-126-3_Vertical
Q2, Q3: Q_PNP_ECB; TO-126-3_Vertical
Q6: MJL21194; TO545P2030X530X2900-3
Q7: MJL21193G; TO545P2030X530X2900-3; PARTREV 7
R16, R17: 1k; R_0805_2012Metric_Pad1.20x1.40mm_HandSolder
R18: 20k; R_1206_3216Metric_Pad1.30x1.75mm_HandSolder
R19, R25, R26: 100; R_0805_2012Metric_Pad1.20x1.40mm_HandSolder
R20, R21: 40k; R_0805_2012Metric_Pad1.20x1.40mm_HandSolder
R22: 3.6k; R_1206_3216Metric_Pad1.30x1.75mm_HandSolder
R23: PV36W102C01B00; POT_PV36W_MUR
R24: 1.1k; R_0805_2012Metric_Pad1.20x1.40mm_HandSolder
R27: 330; R_1206_3216Metric_Pad1.30x1.75mm_HandSolder
R28, R29: 0.33; R_1020_2550Metric_Pad1.33x5.20mm_HandSolder
TP15, TP16, TP17, TP18, TP19, TP20, TP21, TP22, TP23, TP24, TP25: TestPoint; TestPoint_Keystone_5005-5009_Compact
U5: OPA454AIDDA; DDA0008J_NV
U6, U9: MJE15033G; TO-220AB_ONS
U7, U8: MJE15032G; TO-220AB_ONS

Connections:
/AB_Amp/AB_In+: R17.2; also elsewhere on the board
/AB_Amp/AB_In-: JP1.2 (B); also elsewhere on the board
/AB_Amp/OUT: R19.1, TP15.1, U5.6 (OUT)
/AB_Amp/Rf: J4.2, R18.2, R28.2, R29.1, TP24.1
GND: C22.2, C24.1, Q1.1 (E), Q7.2, R25.2, U5.1 (E_D_Com), U5.4 (V-), U6.3 (E), U9.3 (E); also elsewhere on the board
unnamed: JP1.1 (A), JP2.2 (B), R16.1
unnamed: Q1.3 (B), Q4.1 (E), R25.1, TP19.1
unnamed: Q1.2 (C), Q4.3 (B), R20.2
unnamed: Q2.3 (B), Q3.1 (E), R26.2, TP18.1
unnamed: Q2.2 (C), Q3.3 (B), R21.1
unnamed: Q3.2 (C), Q5.2 (C), R22.1, TP16.1, U7.1 (B)
unnamed: Q4.2 (C), Q5.1 (E), R19.2, R24.2, TP17.1, U6.1 (B)
unnamed: Q5.3 (B), R23.2
unnamed: Q6.3, R28.1, TP23.1
unnamed: Q7.3, R29.2, TP22.1
unnamed: R22.2, R23.1
unnamed: R23.3, R24.1
unnamed: C22.1, U5.8 (E_D)
unnamed: C21.1, R17.1, U5.3 (IN+)
unnamed: R16.2, R18.1, U5.2 (IN-)
unnamed: U6.2 (C), U9.1 (B)
unnamed: U7.3 (E), U8.1 (B)
unnamed: Q6.1, R27.1, TP21.1, U8.3 (E)
unnamed: Q7.1, R27.2, TP20.1, U9.2 (C)
V+: C23.1, Q2.1 (E), Q6.2, R26.1, U5.7 (V+), U7.2 (C), U8.2 (C); also elsewhere on the board
VCOM: C21.2, C23.2, C24.2, J4.1, JP2.1 (A), R20.1, R21.2, TP25.1; also elsewhere on the board

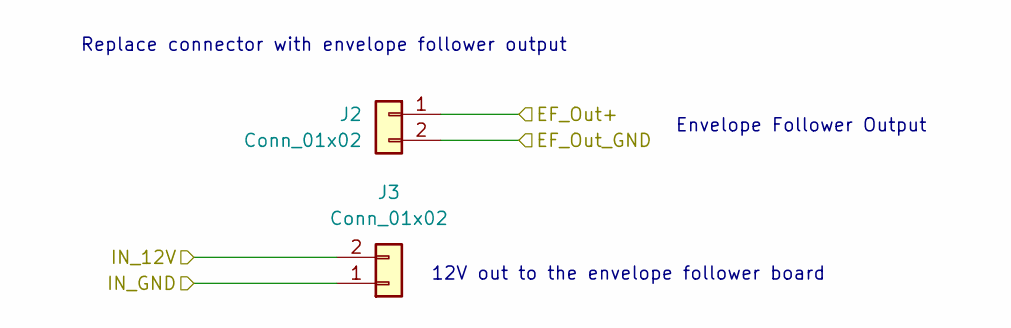
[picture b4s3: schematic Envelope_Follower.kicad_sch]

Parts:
J2, J3: Conn_01x02; TerminalBlock_MaiXu_MX126-5.0-02P_1x02_P5.00mm

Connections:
/AB_Amp/AB_In+: J2.1; also elsewhere on the board
/AB_Amp/AB_In-: J2.2; also elsewhere on the board
GND: J3.1; also elsewhere on the board
VCC: J3.2; also elsewhere on the board

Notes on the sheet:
Envelope Follower Output
Replace connector with envelope follower output
12V out to the envelope follower board
